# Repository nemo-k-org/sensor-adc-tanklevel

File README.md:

# Nemo-K tank level sensor using ADS1115 A/D-converter chip

## Overview

This is Nemo-K board for ESP-01 and ADS1115 (ADS1115IDGSR) A/D-convert chip. The purpose of this sensor
is to read regular tank sensors (senders) giving N-M ohm resistance based on the tank level.

The board sends tank level information to Signal K server.

The board is designed to be used with ESP-01 microcontroller running Nemo-K firmware.

To build you need
 * The PCB
 * ESP-01S

## Content

The repository contains schematics and PCB in KiCad 10.0 format. The footprint properties contains LCSC part numbers
used by [JLCPBC.com](https://jlcpcb.com). If present, the `sensor-sensor-adc-tanklevel/production/` contains all
necessary files to order boards from JLCPCB. The production files can be easily re-created using
[KiCad Fabrication Toolkit](https://github.com/bennymeg/Fabrication-Toolkit).

The Nemo-K project is not affiliated or sponsored by JLCPCB. The project does not endorse JLCPCB.

## Changelog

2026-10-23

## Copyright and License

The license and copyright can be found in the file `LICENSE`.

The license and copyright cover only the schematic diagram and the PCB design. It does not cover footprints and other
embedded elements or technical documentation which may or may not be covered by their own licenses.

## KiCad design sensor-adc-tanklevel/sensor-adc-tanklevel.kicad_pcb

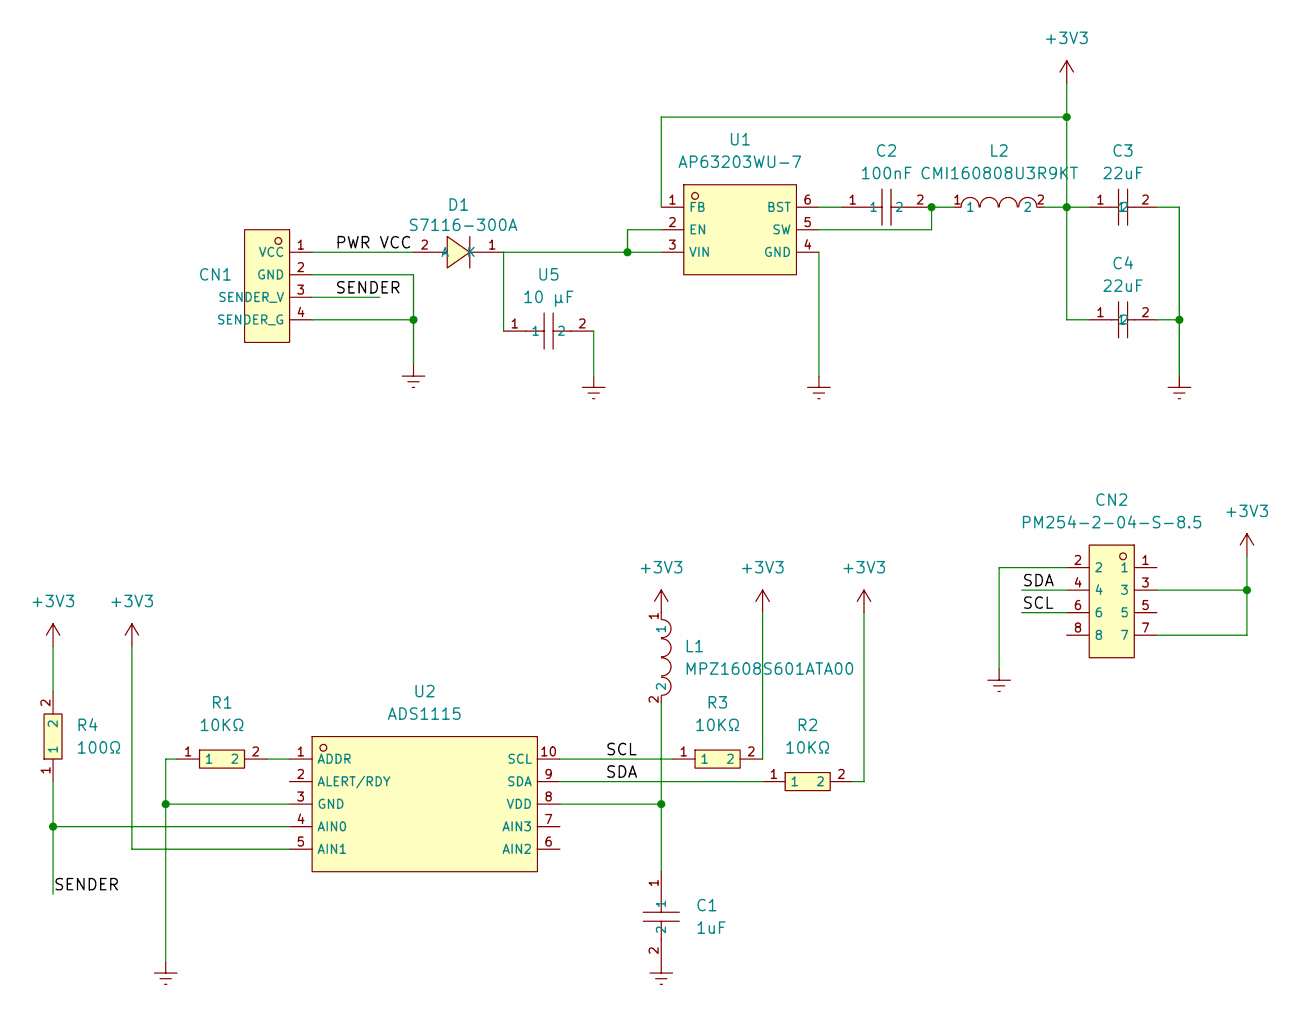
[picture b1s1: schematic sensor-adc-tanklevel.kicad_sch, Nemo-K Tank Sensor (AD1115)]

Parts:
C1: 1uF; C52923_C0402; LCSC C52923
C2: 100nF; C1525_C0402; LCSC C1525
C3, C4: 22uF; C12891_C1206; LCSC C12891
CN1: C5349552_CONN-TH_4P-P3_81_MX127S-3_81-04P-GN01-CU-Y-A; LCSC C5349552
CN2: PM254-2-04-S-8.5; C3975149_HDR-SMD_8P-P2_54-V-F-R2-C4-S7_1; Mfg Part PM254-2-04-S-8.5; LCSC C3975149
D1: S7116-300A; C5174649_SOD-323_L1_7-W1_3-LS2_5-RD; Manufacturer Part S7116-300A; LCSC Part Name S7116-300A
L1: MPZ1608S601ATA00; C107335_L0603; LCSC C107335
L2: CMI160808U3R9KT; C139210_L0603; LCSC C139210
R1, R2, R3: 10KΩ; C25804_R0603; LCSC C25804
R4: 100Ω; C22775_R0603; LCSC C22775
U1: AP63203WU-7; C780769_TSOT-26_L2_9-W1_6-P0_95-LS2_8-BL; LCSC C780769
U2: ADS1115; C37593_MSOP-10_L3_0-W3_0-P0_50-LS5_0-BL; LCSC C37593
U5: 10 µF; C22367827_C0603; LCSC C22367827

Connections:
+3V3: C3.1, C4.1, CN2.3, CN2.7, L1.1, L2.2, R2.2, R3.2, R4.2, U1.1 (FB), U2.5 (AIN1)
/PWR VCC: CN1.1 (VCC), D1.2 (A)
/SCL: CN2.6, R3.1, U2.10 (SCL)
/SDA: CN2.4, R2.1, U2.9 (SDA)
/SENDER: CN1.3 (SENDER_V), R4.1, U2.4 (AIN0)
Earth: C1.2, C3.2, C4.2, CN1.2 (GND), CN1.4 (SENDER_G), CN2.2, R1.1, U1.4 (GND), U2.3 (GND), U5.2
unnamed: D1.1 (K), U1.2 (EN), U1.3 (VIN), U5.1
unnamed: C2.1, U1.6 (BST)
unnamed: C2.2, L2.1, U1.5 (SW)
unnamed: R1.2, U2.1 (ADDR)
unnamed: C1.1, L1.2, U2.8 (VDD)

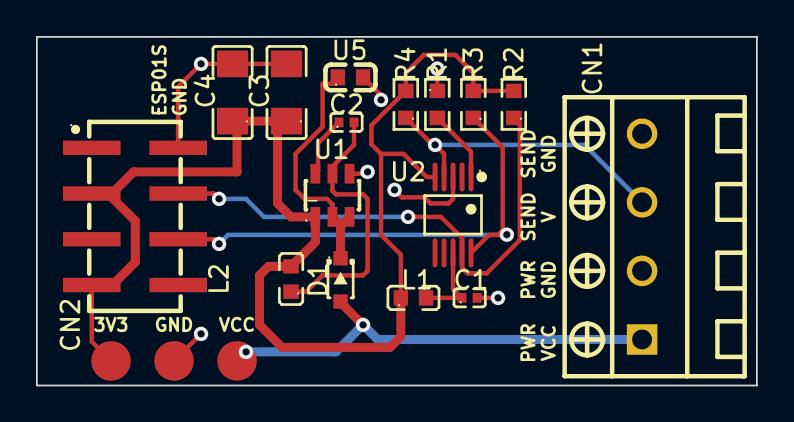
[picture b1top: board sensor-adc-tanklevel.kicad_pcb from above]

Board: 2 copper layers, 40.0 x 19.4 mm, 16 parts (0 on the bottom side), 11 nets.
